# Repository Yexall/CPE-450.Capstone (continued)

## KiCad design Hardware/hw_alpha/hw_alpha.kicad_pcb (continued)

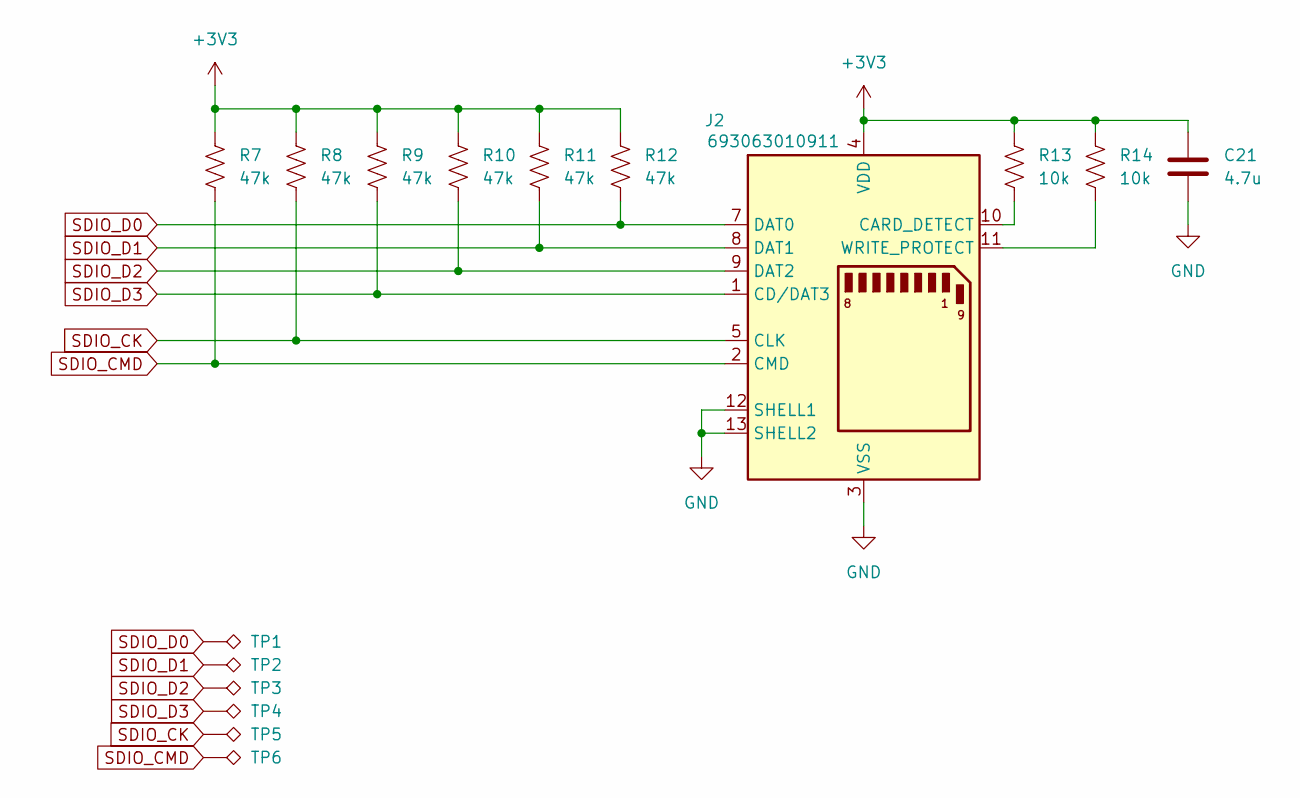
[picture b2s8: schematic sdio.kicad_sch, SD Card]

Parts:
C21: 4.7u; C_0603_1608Metric
J2: 693063010911
R7, R8, R9, R10, R11, R12: 47k; R_0603_1608Metric
R13, R14: 10k; R_0603_1608Metric
TP1, TP2, TP3, TP4, TP5, TP6: TestPoint_Alt; TestPoint_Pad_2.0x2.0mm

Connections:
+3V3: C21.1, J2.4 (VDD), R7.1, R8.1, R9.1, R10.1, R11.1, R12.1, R13.1, R14.1; also elsewhere on the board
GND: C21.2, J2.3 (VSS), J2.6 (VSS), J2.12 (SHELL1), J2.13 (SHELL2); also elsewhere on the board
unnamed: J2.10 (CARD_DETECT), R13.2
unnamed: J2.11 (WRITE_PROTECT), R14.2
SDIO_CK: J2.5 (CLK), R8.2, TP5.1; also elsewhere on the board
SDIO_CMD: J2.2 (CMD), R7.2, TP6.1; also elsewhere on the board
SDIO_D0: J2.7 (DAT0), R12.2, TP1.1; also elsewhere on the board
SDIO_D1: J2.8 (DAT1), R11.2, TP2.1; also elsewhere on the board
SDIO_D2: J2.9 (DAT2), R10.2, TP3.1; also elsewhere on the board
SDIO_D3: J2.1 (CD/DAT3), R9.2, TP4.1; also elsewhere on the board

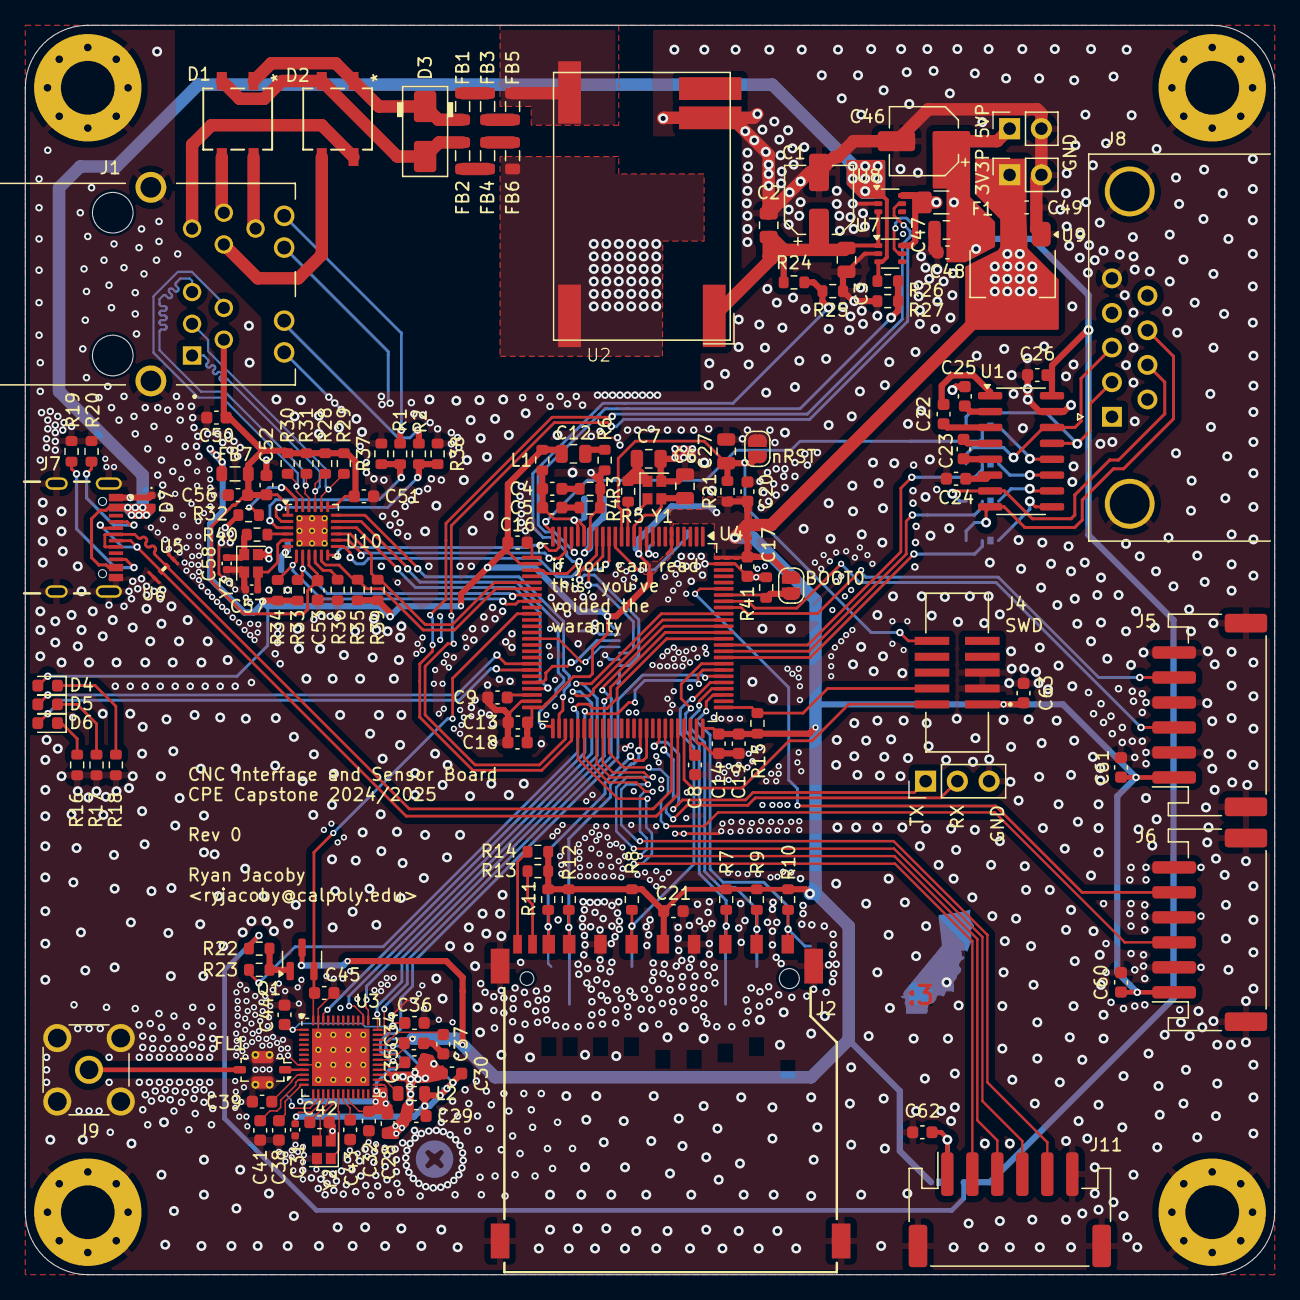
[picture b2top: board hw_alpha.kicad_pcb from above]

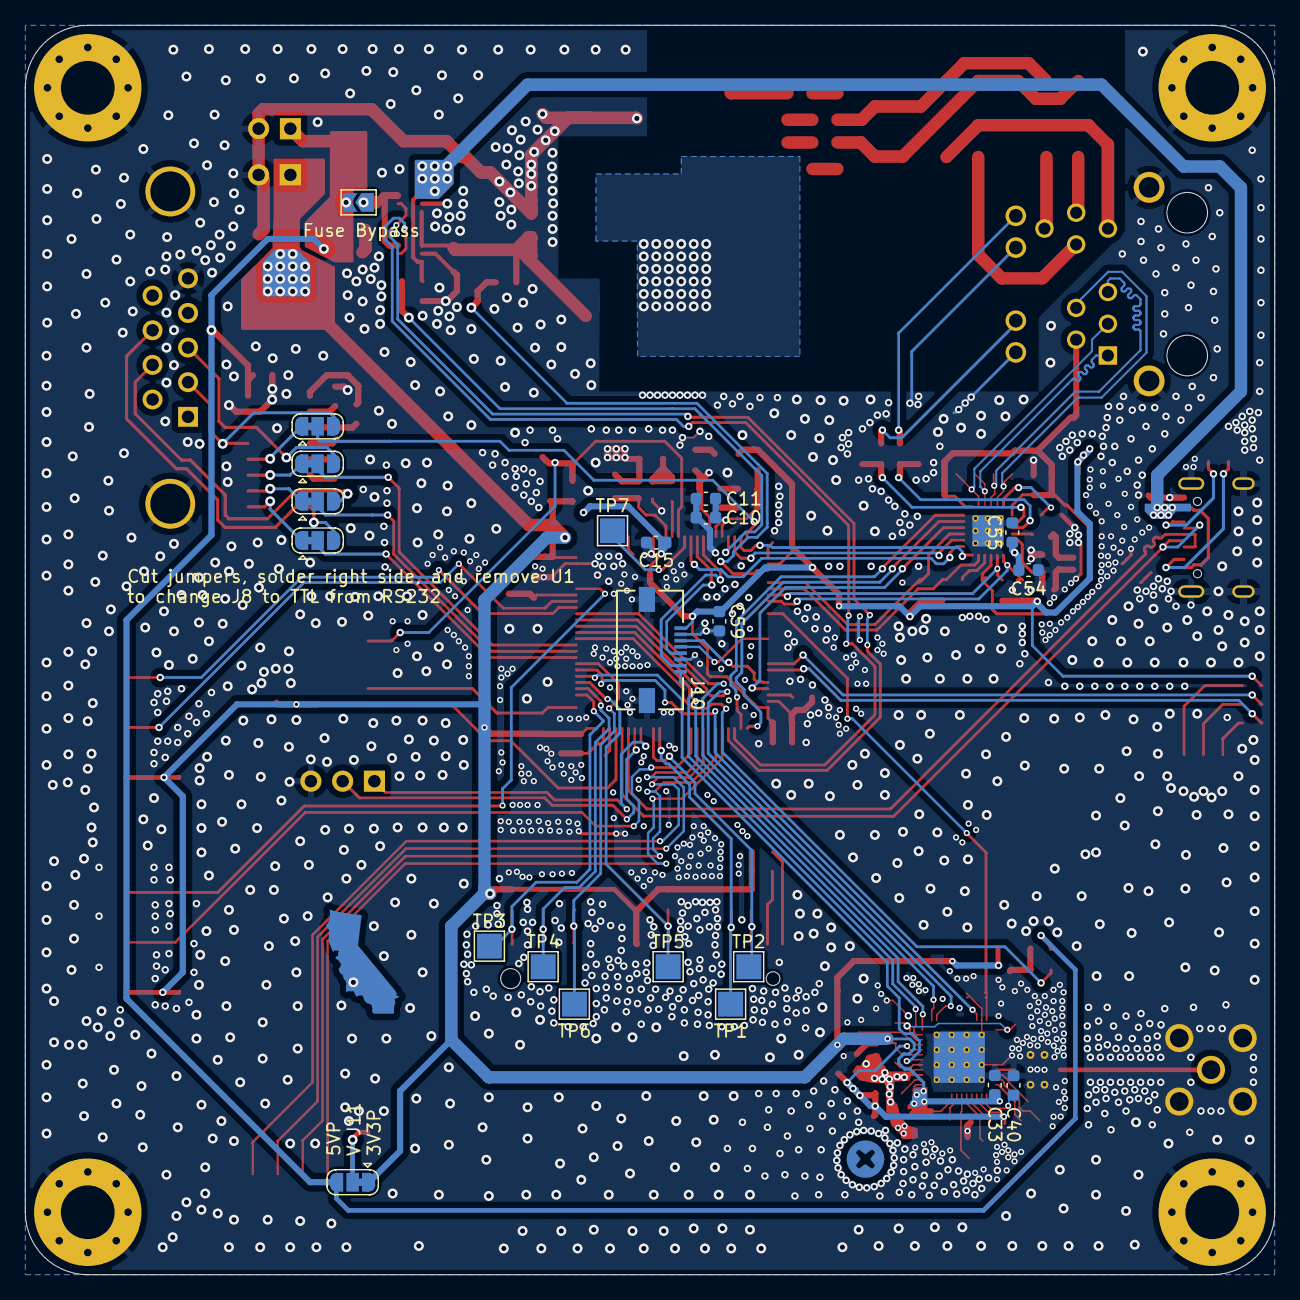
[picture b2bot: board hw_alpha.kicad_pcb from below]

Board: 4 copper layers, 100.0 x 100.0 mm, 168 parts (22 on the bottom side), 135 nets.

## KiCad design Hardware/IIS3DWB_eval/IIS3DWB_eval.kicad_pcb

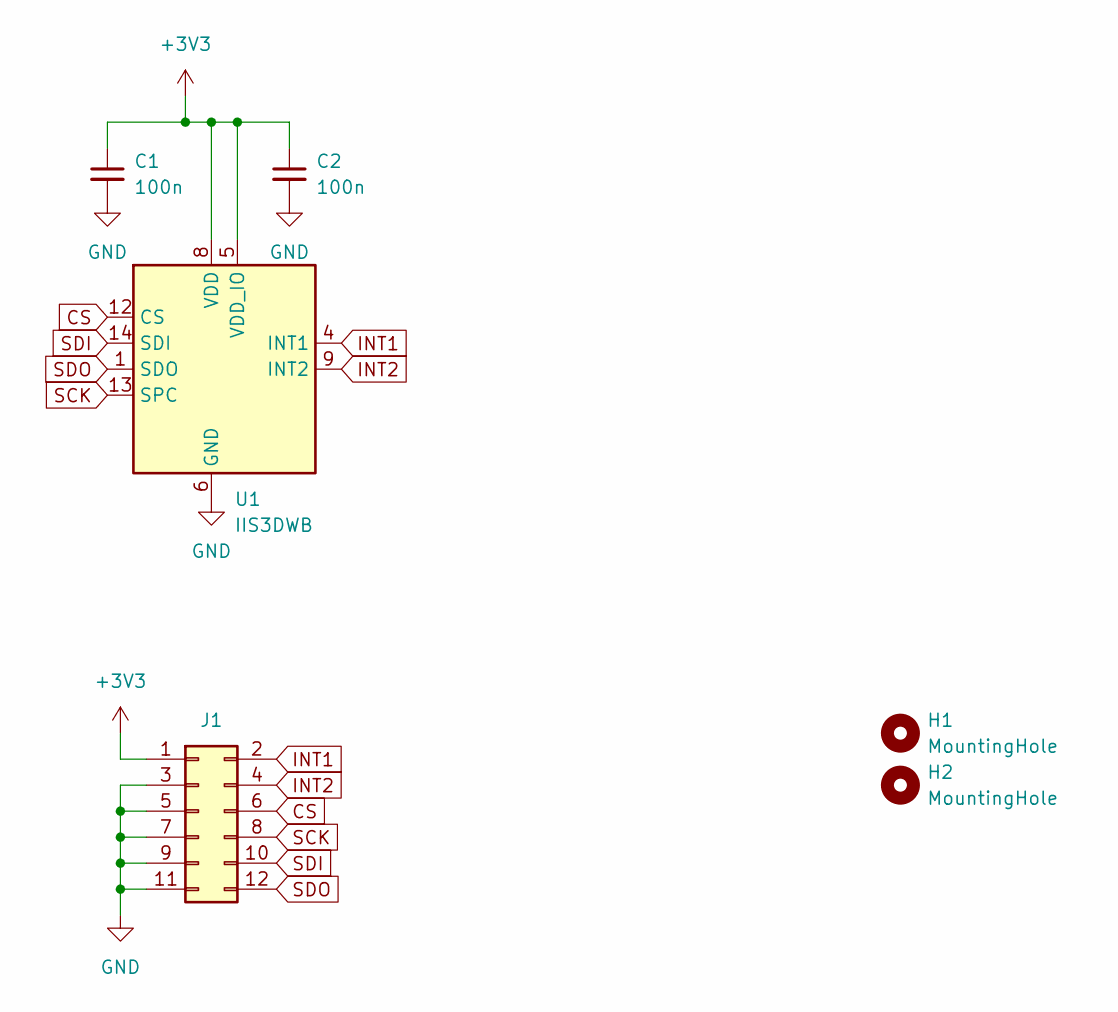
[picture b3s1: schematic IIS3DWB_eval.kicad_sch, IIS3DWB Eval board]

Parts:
C1, C2: 100n; C_0805_2012Metric
H1, H2: MountingHole; MountingHole_2.7mm_M2.5
J1: 2.45mm Pin header; PinHeader_2x06_P2.54mm_Vertical
U1: IIS3DWB; LGA-14_3x2.5mm_P0.5mm_LayoutBorder3x4y; MPN IIS3DWBTR

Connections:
+3V3: C1.1, C2.1, J1.1, U1.5 (VDD_IO), U1.8 (VDD)
CS: J1.6, U1.12 (CS)
GND: C1.2, C2.2, J1.3, J1.5, J1.7, J1.9, J1.11, U1.2 (GND), U1.3 (GND), U1.6 (GND), U1.7 (GND)
INT1: J1.2, U1.4 (INT1)
INT2: J1.4, U1.9 (INT2)
SCK: J1.8, U1.13 (SPC)
SDI: J1.10, U1.14 (SDI)
SDO: J1.12, U1.1 (SDO)

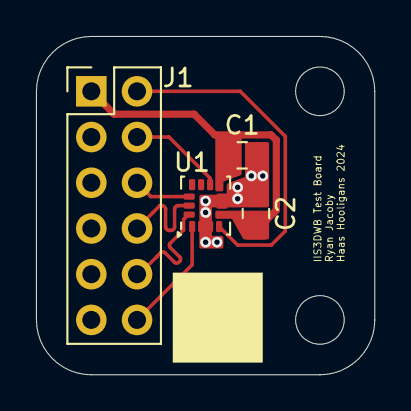
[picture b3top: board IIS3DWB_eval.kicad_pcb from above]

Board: 2 copper layers, 18.8 x 18.8 mm, 6 parts (0 on the bottom side), 8 nets.

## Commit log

2025-03-19 HW initial commit
2025-03-24 Add hardware license and fix BOM issues
2025-04-04 Add report/poster and hw_alpha mod doc updates
